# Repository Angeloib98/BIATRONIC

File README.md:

# README!!!!

* [Horario de Reuniones](#horario-reuniones)
* [Roles](#roles)
* [Responsabilidades administrativas](#responsabilidades-administrativas)
* [Responsabilidaes técnicas](#responsabilidades-técnicas)
* [Bitácora](#bitácora)

## Horario de reuniones

Martes 5:00 pm a 7:00 pm

Sabado 6:00 pm a 8:00 pm

## Roles
| Nombre                  | Rol administrativo         | Rol técnico |
| ---                     | ---                        | ---         |
| Marco Zolla             | Administrador de proyecto  | Ingenierio en Sistemas |
| Heiner Amador           | Documentador               | Diseño Mecánico |
| Robert Cerdas           | Business Intelligence      | Lider técnico |
| Manuel Garita           | Líder administrativo       | Verificación y Validación  |
| Karen Guadamuz          | Gestora de calidad         | Normas |
| Angelo Isaac            | Secretario                 | Ingenieria de software | 
| Adrián Nuñez            | Gestor de riesgos          | Cálculo y simulación |
| Francinnie Rodriguez    | Asesora financiera         | Integrador | 
| Brayan Solís            | Gestor de tiempo           | Ingenieria de hardware |
 
## Responsabilidades administrativas
| Roles                    | Responsabilidad |
| ---                      | --- |
| Adminstrador de proyecto | Comunicación con el sponsor, verificar que todos los objetivos se cumplan, establecer cada tarea que se tiene que hacer, lidera las reuniones y                                    hacer informes de cada reunión. |
| Business Intelligence    | se encuentra envuelto en un proceso interactivo en el que explora y analiza información estructurada sobre un área (normalmente almacenada en un                                    datawarehouse), para descubrir tendencias o patrones, a partir de los cuales derivar ideas y extraer conclusiones. |
| Lider administrativo     | Unión de cada segmento, verificar que todo este funcionando bien y en armonía y comunicación con administrador de proyectos, delegar las tareas.|
| Secretario               | El puesto de secretarı́a tiene como responsabilidades encargarse del área administrativa, asistir a los puestos gerenciales o ejecutivos en términos                                de anotaciones, agenda y manejo de comunicaciones. Para este puesto es vital tener habilidades organizativas y atención al detalle. |
| Gestor de riesgos        | Identificación de riesgos, análisis cuantitativo y cualitativo de riesgos planificación de respuesta de riesgos. |
| Gestor de Tiempo         | Herramientas y control de agenda, duración de actividades,  estimación de recursos, programación del Proyecto, secuencia de actividades. | 
| Asesor financiero        | Planificación de las compras y adquisiciones, tipos de contratación, estimación de costos, histograma de recursos, presupuesto (integración y                                      alcance) y control presupuestario. |
| Gestor de calidad        | Procesos de gestión, plan de administración de calidad, control de calidad. |
| Documentador             | Documentación del proyecto. |

## Responsabilidades técnicas
| Roles                        | Responsabilidad |
| ---                          | --- |
| Líder técnico                | Poner objetivos  y distribuir asignaciones, además de verificar que no hayan problemas  durante el tiempo del proyecto.|
| Integrador                   | Se encargan de unir componentes independientes incluso de diferentes proveedores– para crear un sistema único, adecuado a la realidad y tareas                                    particulares de una compañı́a |
| Ingeniero de Hardware        | Diseño de pcb y circuitos.|
| Ingeniero de Software        | Diseño de aplicaciones y programaciones.|
| Verificación y validación    | Benchmarks y crear métodos para verificar el funcionamiento del proyecto. |
| Diseño mecánico              | Encargado del diseño mecánico o estructural es la persona responsable de la elección de componentes y materiales y del diseño fı́sico del                                          ensamble del producto mediante herramientas CAD según las especificaciones y requerimientos del problema. | 
| Simulaciones y cálculos      | Persona encargada de estudiar y describir la comprensión de los elementos de un sistema de interés, teniendo en cuenta las caracterı́sticas                                        esenciales del mismo, obteniendo ası́ un modelo matemático que describa el comportamiento del mismo |
| Ingenierio en sistemas       | Encargado de crear las interfaces entre los distintos sistemas del proyecto |
| Normas                       | Revisar las normas necesarias para el proyecto, tanto técnicas como normas ambientales a seguir, como en el tipo de material a utilizar.  |

## Bitácora

### 05 agosto

**Objetivos de la reunión:**

**Resumen de la reunión:**

Corregimos los roles: agregamos ing.sistemas, simulaciones y calculos, integrador, secretario y business intelligence

Escogimos nuevo horario: Martes 5:00 pm a 7:00 pm
                         Sabado 6:00 pm a 8:00 pm
                         
Arreglamos la matriz R&R : se hizo más especifica y se agregaron los roles a cada persona

Se duró mucho en la reunión por lo que se dejó hasta aqui, y relevamos las asignaciones para revisar el sabado (se ven en los issues).

### 06 agosto

**Sesión extraordinaria**

Se hizo una tabla con los involucrados en el proyecto, además de esto, se decidió que cada persona asignada iba a hacer la caracterzación y gestión de cada invoucrado.

### 07 agosto

**Asistencia**
1. Robert Cerdas: enfermo
2. Adrian Nuñez: se fue en media reunión, por perdida de datos
3. Manuel: Llegó tarde

**Objetivos de la reunión:**

- Determinar nombre de la empresa y del producto.
- Revisar lo que faltó de la semana pasada (herramientas, escalación, RACI).
- Revisar análisis de involucrados (caracterización, estrategia).
- Revisar paquetes de trabajo y Gantt.
- Afinar lo que falte de lo revisado.
- Delegar tareas para la presentación.

**Otro aspecto importante:**

Angelo Isaac dio un minitutorial de como utilizar github y github desktop.

### 09 agosto

**Sesión extraordinaria**

Empezando se explicó rapidamente lo que se dijo en consulta con el profesor para luego revisar la presentación para mejorar detalles de formato y qué debe y no debe ir, ademas se dividió la misma. Finalmente se explicó que debemos agregar la tabla de involucros propuesta por Manuel Zolla.

### 10 agosto

**Asistencia** 

Todos asistieron

**Objetivo de la reunión**

- Hablar de la retroalimentancio de la presentación de semana 3

**Otro aspecto importante**

Preguntar al profesor en consulta acerca de si los clientes los quiere delimitados para la presentación de semana 5 o los necesita todos los posibles clientes.

### 14 agosto

**Asistencia**

Adrián Nuñez falto debido a una cena familiar

Heiner Amador llgea tarde

Francinnie llega tarde

**Objetivos de la reunión**

- Revisar el trabajo de investigación de normas
- Revisar el trabajo del área de Business intelligence: gestión de segmentos de clientes, propuestas de valor, valor del mercado elegido...
- Establecer la misión, visión y valores organizacionales

**Otros aspectos importantes**

Se delegó el último punto para hacer tareas.

### 17 agosto

**Asistencia**

Karen Guadamuz llegó tarde 50 minutos

**Objetivos de la reunión**

- Hablar de la tarea 

- Hablar de la retroalimentación

**Otros aspectos importantes**

Revisamos las normas hechas por Karen

### 21 agosto (corte antes de reporte base)

**Asistencia**

Karen Guadamuz 15 min tarde

Adrian Nuñez 30 min tarde y se fue faltando una hora

**Objetivos de la reunión**

- Revisar todas las partes del reporte base
- Hacer correcciones si fuera necesario
- Discutir sobre la presentación
- Discutir un mecanismo de retroalimentación

**Otros aspectos importantes**

### 07 setiembre 

**Asistencia**

Robert se ausentó

**Objetivos de la reunión**

- Dividirnos el trabajo de SyRS, SRS y validación
- Hablar de entrevistas con personas relacionadas al producto

**Otros aspectos importantes**

### 11 setiembre 

**Asistencia**

**Objetivos de la reunión**

- Discutir la encuesta
- Discutir la entrevista
- Discutir la SyRS

**Otros aspectos importantes**

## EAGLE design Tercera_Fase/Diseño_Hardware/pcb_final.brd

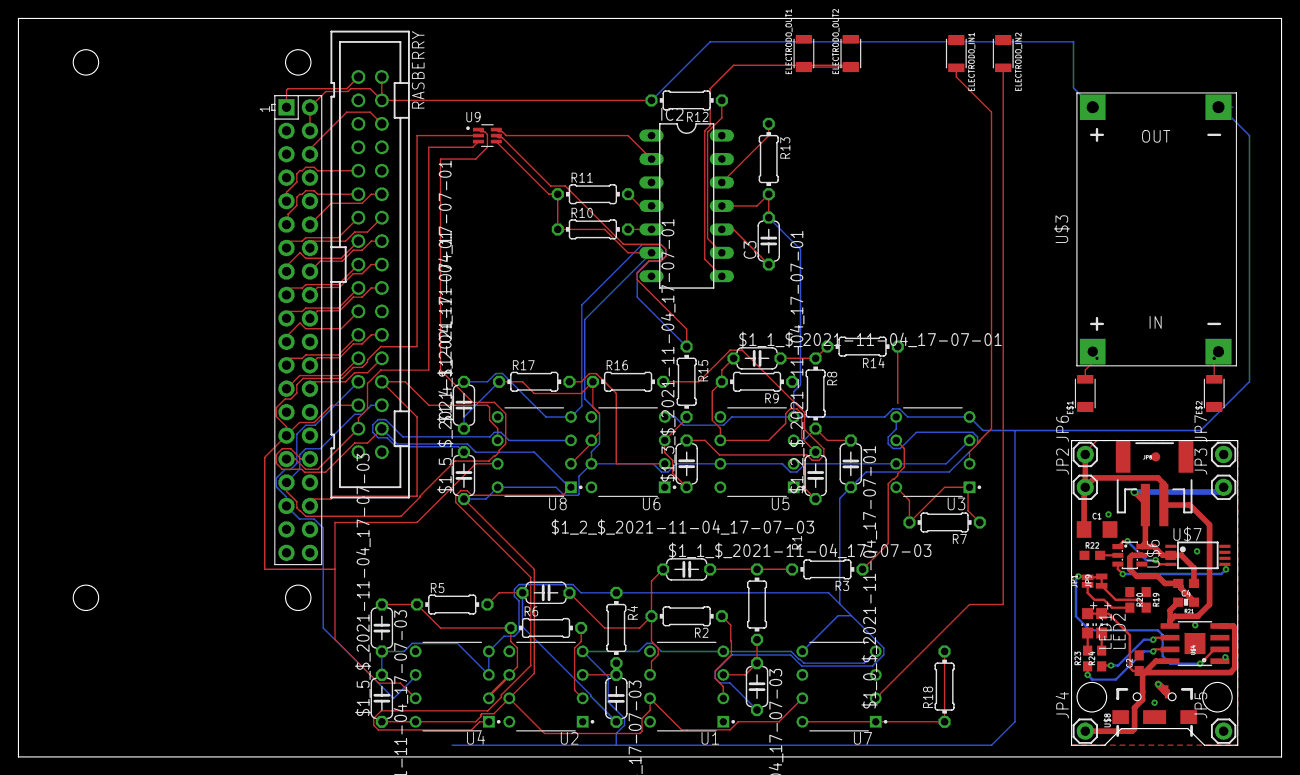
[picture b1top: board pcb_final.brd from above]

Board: 2 copper layers, 136.8 x 80.0 mm, 80 parts (0 on the bottom side), 72 nets.

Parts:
$1_0_$_2021-11-04_17-07-01, $1_0_$_2021-11-04_17-07-03, $1_2_$_2021-11-04_17-07-01, $1_2_$_2021-11-04_17-07-03, $1_3_$_2021-11-04_17-07-01, $1_3_$_2021-11-04_17-07-03: 100p; C050-024X044
$1_1_$_2021-11-04_17-07-01, $1_1_$_2021-11-04_17-07-03: 200p; C050-024X044
$1_4_$_2021-11-04_17-07-01, $1_4_$_2021-11-04_17-07-03: 100n; C050-024X044
$1_5_$_2021-11-04_17-07-01, $1_5_$_2021-11-04_17-07-03: 10u; C050-024X044
C1: 10uF; 1206
C2: 1.0uF; 0603
C3: 1.3n; C050-024X044
C4: 0.1uF; 0603
E$1, E$2: RESC3115X65N_1623693-1
ELECTRODO_IN1, ELECTRODO_IN2: 1623693-1; RESC3115X65N_1623693-1
ELECTRODO_OUT1, ELECTRODO_OUT2: 1623693-1; RESC3115X65N_1623693-1
IC2: ICL8038
JP1: JUMPER NO; SMT-JUMPER_2_NO_NO-SILK
JP2: BAT; 1X01
JP3: GND-BAT; 1X01
JP4: IN+; 1X01
JP5: IN-; 1X01
JP6: OUT+; 1X01
JP7: OUT-; 1X01
JP8: JST; JST-2-SMD
JP9: JUMPER NC; SMT-JUMPER_2_NC_TRACE_NO-SILK
LED1: red; CHIP-LED0805
LED2: green; CHIP-LED0805
R1, R3, R8, R14: 1.8k; 0204/7
R2, R9: 2.6k; 0204/7
R4, R15: 45k; 0204/7
R5, R6, R16, R17: 22.5k; 0204/7
R7, R18: 250; 0204/7
R10, R11: 4k; 0204/7
R12: 10k; 0204/7
R13: 81k; 0204/7
R19: 2.4k; 0603
R20: 4.7k; 0603
R21: 100; 0603-RES
R22: 1k; 0603
R23, R24: 330; 0603
RASBERRY: 2534-; PAK100/2500-34
U1, U2, U5, U6: UA741CP; DIP794W45P254L959H508Q8
U3, U7: INA114AP; DIP794W45P254L959H508Q8
U4, U8: ADC0831CCN; DIP794W45P254L959H508Q8
U9: DAC5311IDCKRQ1; SOT65P210X110-6N
U$1: RPI-ZERO; RASPBERRYPI_BASTELSTUBE_V13_RASPI_BOARD_B+_FULL
U$3: DC-DC-STEP-UP-MT3608
U$4: DIO5158; SOIC-8
U$5: FIDUCIAL; FIDUCIAL_1MM
U$6: DW01-P; SOT23-6L
U$7: FS8205A; TSSOP8
U$8: USB-MICROB-POWERONLY
U$9: LOGO-3MM
U$10: E-R.IO-3MM
U$11: OSH-3MM
U$12: LOGO-BACK-6MM
U$13: E-R.IO-BACK-6MM

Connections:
3V3@1: RASBERRY.1, U$1.1
3V3@2: RASBERRY.17, U$1.17
5V0@2: $1_5_$_2021-11-04_17-07-01.1, $1_5_$_2021-11-04_17-07-03.1, IC2.6, R10.1, R11.1, U1.7, U2.7, U3.3, U3.7, U4.8, U5.7, U6.7, U7.7, U8.8, U9.4
BAT: C1.1, JP2.1, JP6.1, JP8.2, R21.2, U$4.5
CHRG: R23.1, U$4.7
DONE: R24.1, U$4.6
GND: $1_0_$_2021-11-04_17-07-01.2, $1_0_$_2021-11-04_17-07-03.2, $1_4_$_2021-11-04_17-07-03.2, $1_5_$_2021-11-04_17-07-03.2, R4.1, U3.5, U4.3, U4.4, U7.5
GND-ISO: C4.1, JP3.1, JP8.1, U$6.6, U$7.2, U$7.3
GND@1: RASBERRY.9, U$1.9
GND@2: RASBERRY.25, U$1.25
GND@4: RASBERRY.14, U$1.14
GND@5: RASBERRY.20, U$1.20
GND@8: RASBERRY.6, U$1.6
ISET: JP1.2, JP9.2, U$4.2
LED1: LED1.C, R23.2
LED2: LED2.C, R24.2
unnamed: $1_1_$_2021-11-04_17-07-03.2, R1.1, R3.2
unnamed: $1_0_$_2021-11-04_17-07-03.1, R1.2, U1.3
unnamed: R2.1, U1.2
unnamed: $1_4_$_2021-11-04_17-07-03.1, R5.1, R6.1, U2.6, U4.2
unnamed: R7.1, R7.2, U3.1, U3.8
unnamed: $1_1_$_2021-11-04_17-07-03.1, $1_2_$_2021-11-04_17-07-03.2, R2.2, U1.6
unnamed: $1_2_$_2021-11-04_17-07-03.1, $1_3_$_2021-11-04_17-07-03.2, R5.2
unnamed: $1_3_$_2021-11-04_17-07-03.1, R4.2, U2.3
unnamed: R6.2, U2.2
unnamed: R3.1, U3.6
unnamed: $1_1_$_2021-11-04_17-07-01.2, R8.1, R14.2
unnamed: $1_0_$_2021-11-04_17-07-01.1, R8.2, U5.3
unnamed: RASBERRY.29, U4.7, U8.7, U9.2, U$1.29
unnamed: RASBERRY.11, U$1.11
unnamed: R9.1, U5.2
unnamed: $1_1_$_2021-11-04_17-07-01.1, $1_2_$_2021-11-04_17-07-01.2, R9.2, U5.6
unnamed: $1_2_$_2021-11-04_17-07-01.1, $1_3_$_2021-11-04_17-07-01.2, R16.2
unnamed: $1_3_$_2021-11-04_17-07-01.1, R15.2, U6.3
unnamed: R17.2, U6.2
unnamed: IC2.4, R11.2
unnamed: IC2.5, R10.2
unnamed: C3.1, IC2.10
unnamed: IC2.9, R12.1
unnamed: IC2.2, U9.6
unnamed: ELECTRODO_OUT1.1, ELECTRODO_OUT2.1, IC2.8
unnamed: IC2.12, R13.1
unnamed: $1_4_$_2021-11-04_17-07-01.1, R16.1, R17.1, U6.6, U8.2
unnamed: R18.1, R18.2, U7.1, U7.8
unnamed: RASBERRY.27, U4.6, U$1.35
unnamed: RASBERRY.15, U$1.15
unnamed: RASBERRY.19, U$1.19
unnamed: RASBERRY.28, U8.6, U$1.36
unnamed: RASBERRY.31, U9.3, U$1.31
unnamed: RASBERRY.30, U9.1, U$1.33
unnamed: RASBERRY.21, U$1.21
unnamed: RASBERRY.13, U$1.13
unnamed: RASBERRY.23, U$1.23
unnamed: RASBERRY.24, U$1.24
unnamed: RASBERRY.26, U$1.26
unnamed: RASBERRY.12, U$1.12
unnamed: RASBERRY.16, U$1.16
unnamed: RASBERRY.18, U$1.18
unnamed: RASBERRY.32, U4.1, U8.1, U$1.32
unnamed: JP9.1, R19.2
unnamed: JP1.1, R20.2
unnamed: R22.2, U$6.2
unnamed: U$6.3, U$7.5
unnamed: C3.2, IC2.11, R13.2, U1.4, U2.4, U3.4, U5.4, U6.4, U7.4, U$3.OUT-
unnamed: ELECTRODO_IN2.2, U7.2
unnamed: ELECTRODO_IN1.2, U3.2
OD: U$6.1, U$7.4
S$1: $1_4_$_2021-11-04_17-07-01.2, $1_5_$_2021-11-04_17-07-01.2, R15.1, U8.3, U8.4, U9.5
S$2: R12.2, RASBERRY.2, RASBERRY.4, U$1.2, U$1.4, U$3.OUT+
S$3: C1.2, C2.2, JP5.1, JP7.1, R19.1, R20.1, R22.1, U$4.1, U$4.3, U$7.6, U$7.7, U$8.GND
VCC: C2.1, JP4.1, LED1.A, LED2.A, U$4.4, U$4.8, U$8.VBUS
VCC-DW: C4.2, R21.1, U$6.5

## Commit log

2021-08-05 referencias agregadas
2021-08-06 Agregue carpeta de primera fase
2021-08-07 sesion extraordinaria 06 agosto
2021-08-08 Analisis de involucrados
2021-08-08 Agregue prueba
2021-08-08 bitacora 7/8/2021
2021-08-08 Agregado análisis de involucrados para proveedores
2021-08-08 Análisis y estrategia Clientes
    Agregué al word la caracterización y la estrategia de gestión y comunicación de los involucrados para los clientes.
2021-08-09 Regulacion
    Caracterización de los involucrados y documentar estrategia de gestión para regulacion
2021-08-09 arreglo de formato
2021-08-10 agregada tabla de interes proveedores y regulacion
2021-08-10 sesion extraordinaria 09/08/21
2021-08-10 Agregue carpetas
2021-08-10 quite un archivo perdido
2021-08-10 Add files via upload
    Matriz RACI Versión final de semana 3
2021-08-11 Add files via upload
    RACI Semana 3
2021-08-11 bitacora 10 agosto
2021-08-15 bitacora 14 agosto
2021-08-16 Canvas_business_intelligence
    Se incluye la parte del canvas del business intelligence
2021-08-16 Agregado plan de enfoque (misión, visión,...)
2021-08-18 bitacora 17 agosto
2021-08-18 Agregado documento con análisis de alcances.
2021-08-18 cambiada misión, agregadas correcciones a alcances
2021-08-20 Canvas y tabla segmentos clientes
    Se actualizo la tabla de segmentos de clientes y el canvas
2021-08-20 Socios
    Cambio a los socios del canvas
2021-08-21 Add files via upload
    Ultima versión de organigrama para semana 5
2021-08-21 Cambio de segmento
2021-08-22 bitacora 21 agosto
2021-08-22 Bitácora 21 agosto
2021-08-29 agregados casos de uso
2021-08-31 corregidos casos de uso
2021-09-07 archivo SRS de reqview
2021-09-08 Add files via upload
    Concepto de operaciones
2021-09-08 Agregado borrador SyRS
2021-09-09 Agregadas referencias de Mariana
2021-09-10 documento base
2021-09-11 SyRS - Adrián Núñez
    Se agregaron las partes asignadas de mantenibilidad, fiabilidad, otras cualidades y modos y estados del sistema.
2021-09-11 agregue parte de robert (prueba)
2021-09-11 interfaz de usuraio, hardware y sistema
2021-09-12 Documento SyRS
    Requerimientos asignados - Adrián Núñez
2021-09-12 Corrección gramatical
    Cambio de una pequeña parte
2021-09-13 Agregado SyRS
2021-09-16 afinando el srs
2021-09-16 agrega pdf
2021-09-21 Agregado diagrama casos de uso nuevo
2021-09-21 Add files via upload
    Proyecto BIA de referencia
2021-09-21 Updateado diagrama casos uso
2021-09-22 agregado requerimiento SyRS encendido/apagado
2021-09-22 Agregadas Pugh Marco
2021-09-22 Cambios consulta
2021-09-24 Algunas correcciones a requerimientos agregadas
2021-09-24 Terminadas correcciones SyRS
2021-09-25 agregado requerimiento SyRS-153
2021-09-26 Matriz Pugh - Adrián Núñez
    Agregué mi pestaña extra con mi nombre con las matrices pugh de los subproblemas asignados
2021-09-27 arreglo del srs
2021-09-27 arreglo srs
2021-09-30 Agregados requerimientos Heiner
2021-10-01 Actualizaciones para software
2021-10-01 Added DiagramaClases.drawio
2021-10-02 Agregado BDD composicion funcional
2021-10-03 N2 Charts Sistemas Manuel
2021-10-04 IBD SysML
    Diagrama IBD
2021-10-04 Modos en Concepto de Operaciones
    Agregué los modos de requerimientos el en el concepto de operaciones
2021-10-05 Updated bdd sys
2021-10-06 Correcciones
    Correcciones IBD y Concepto de Operaciones
2021-10-06 Revert "Merge branch 'main' of https://github.com/Angeloib98/BIATRONIC into main"
    This reverts commit e8cc4815cec9e0ee26ced7827a627716654c9622, reversing
    changes made to 5ef86c3a38f954b73ce693dc2352bbfe88b3a0fa.
2021-10-06 Revert "Revert "Merge branch 'main' of https://github.com/Angeloib98/BIATRONIC into main""
    This reverts commit 2e4d70230ea1de34565241186ab5cb2e037e471b.
2021-10-09 Agregados diagramas de flujo
2021-10-09 Agregado recomendaciones a casos de uso
2021-10-10 pdf_fix
2021-10-10 pdf tabla
2021-10-10 IBD - colores
    agregué colores al ibd como recomendó el profe
2021-10-10 colores
    Colores como los de Robert en el IBD de software
2021-10-10 Agregadas versiones pdf de requerimientos
2021-10-10 Agregadas tablas casos uso
2021-10-10 agregado diagrama de flujo grande
2021-10-11 pngs de las arquitecturas
2021-10-25 IBD Sistemas
    Acondicionamiento de señal
2021-10-30 Folder tercera fase creado
2021-10-30 folder de software
2021-10-30 Added Diagrama_Estados.drawio
2021-10-30 Added Diagrama_General.drawio
2021-10-30 Added Diagrama_Inicio_Sesion
2021-10-30 Update Diagrama_Inicio_Sesion
2021-10-30 Added Diagrama_ajustes
2021-10-30 Update Diagrama_ajustes
2021-10-30 Added Diagrama_medicion
2021-10-30 Update Diagrama_medicion
2021-10-31 libro circuitos utiles
2021-10-31 Referencia sintetizadores
2021-11-01 agregadas recetas yocto con dependencias
2021-11-01 Diagrama de calculos
    resumen en diagrama de investigación de cálculos
2021-11-01 Agregadas propuestas iniciales para la interfaz
2021-11-02 Added Diagrama_Comunicacion
2021-11-02 Update Diagrama_Comunicacion
2021-11-02 Added Diagrama_Anomalias
2021-11-02 Update Diagrama_Anomalias
2021-11-04 Agregada nueva iteración de gui
2021-11-04 Referencias y método de gestión de riesgos
2021-11-05 Terminada tabla dependencias
2021-11-06 Added Diagrama_Seleccion_Usuario
2021-11-06 Update Diagrama_Seleccion_Usuario
2021-11-07 Added Diagrama_App.drawio
2021-11-07 agrego imagenes de la app
2021-11-07 pdf actualizado
2021-11-07 Create Integración
2021-11-07 Ajustadas interfaces dispositivo
2021-11-09 actualizacion app
2021-11-11 referencia
    Cálculos de bioimpedancia
2021-11-13 Diseño PCB

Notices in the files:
parts and their libraries:
SparkFun-Capacitors: Licensing: Creative Commons ShareAlike 4.0 International - https://creativecommons.org/licenses/by-sa/4.0
SparkFun: Licensing: CC v3.0 Share-Alike You are welcome to use this library for commercial purposes.
